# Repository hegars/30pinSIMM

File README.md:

# 4 MByte Fast Page Mode Dynamic Random Access Memory 30 pin Single Inline Memory Module

KiCAD design for a 4MByte 30 pin SIMM Fast Page Mode Dynamic Random Access Memory Module Design
 
WORK IN PROGRESS - Dont let your blue smoke out.

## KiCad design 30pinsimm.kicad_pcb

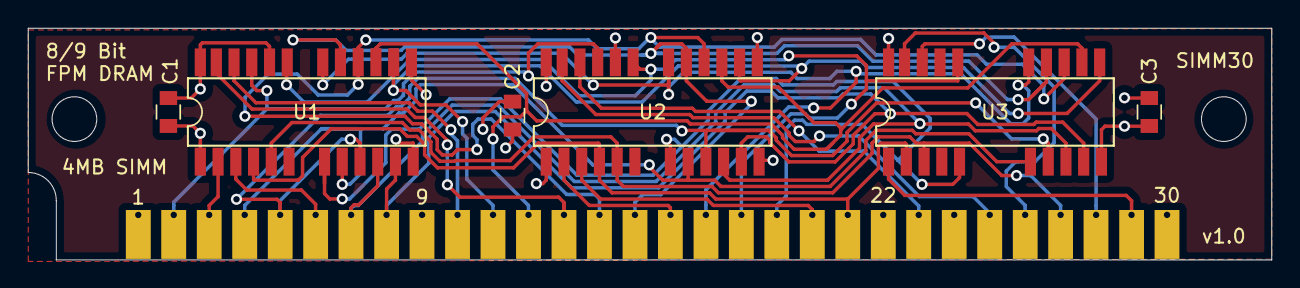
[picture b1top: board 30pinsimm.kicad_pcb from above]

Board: 4 copper layers, 89.0 x 16.6 mm, 7 parts (0 on the bottom side), 27 nets.

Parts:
C1, C2, C3: C; C_0805
SIMM30: 30pinSIMM
U1, U2: 4Mx4FPMDRAM; SOJ-24
U3: 4Mx1FPMDRAM; SOJ-20

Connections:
+5V: C1.2, C2.2, C3.2, SIMM30.1, SIMM30.30, U1.1, U1.13, U2.1, U2.13, U3.13
/A0: SIMM30.4, U1.9, U2.9, U3.9
/A1: SIMM30.5, U1.10, U2.10, U3.10
/A2: SIMM30.7, U1.11, U2.11, U3.11
/A3: SIMM30.8, U1.12, U2.12, U3.12
/A4: SIMM30.11, U1.15, U2.15, U3.14
/A5: SIMM30.12, U1.16, U2.16, U3.15
/A6: SIMM30.14, U1.17, U2.17, U3.16
/A7: SIMM30.15, U1.18, U2.18, U3.17
/A8: SIMM30.17, U1.19, U2.19, U3.18
/A9: SIMM30.18, U1.21, U2.21, U3.22
/A10: SIMM30.19, U1.8, U2.8, U3.5
/CAS: SIMM30.2, U1.23, U2.23
/CASP: SIMM30.28, U3.24
/DP: SIMM30.29, U3.1
/DQ0: SIMM30.3, U1.2
/DQ1: SIMM30.6, U1.3
/DQ2: SIMM30.10, U1.24
/DQ3: SIMM30.13, U1.25
/DQ4: SIMM30.16, U2.2
/DQ5: SIMM30.20, U2.3
/DQ6: SIMM30.23, U2.24
/DQ7: SIMM30.25, U2.25
/QP: SIMM30.26, U3.25
/RAS: SIMM30.27, U1.5, U2.5, U3.3
/WE: SIMM30.21, U1.4, U2.4, U3.2
GND: C1.1, C2.1, C3.1, SIMM30.9, SIMM30.22, U1.14, U1.22, U1.26, U2.14, U2.22, U2.26, U3.26

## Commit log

2021-01-01 moving files around
2021-01-01 alingment
2021-01-02 updated the 4Mb module
2021-01-02 general updates
2021-01-02 2sig 2 pwr layer routing
2021-01-02 added gerbers
2021-01-03 update gerbers
2021-01-03 updated gerbers
2021-01-04 issue version 1.0
2021-01-10 min hole size to 0.45mm
2021-01-10 update drill files
